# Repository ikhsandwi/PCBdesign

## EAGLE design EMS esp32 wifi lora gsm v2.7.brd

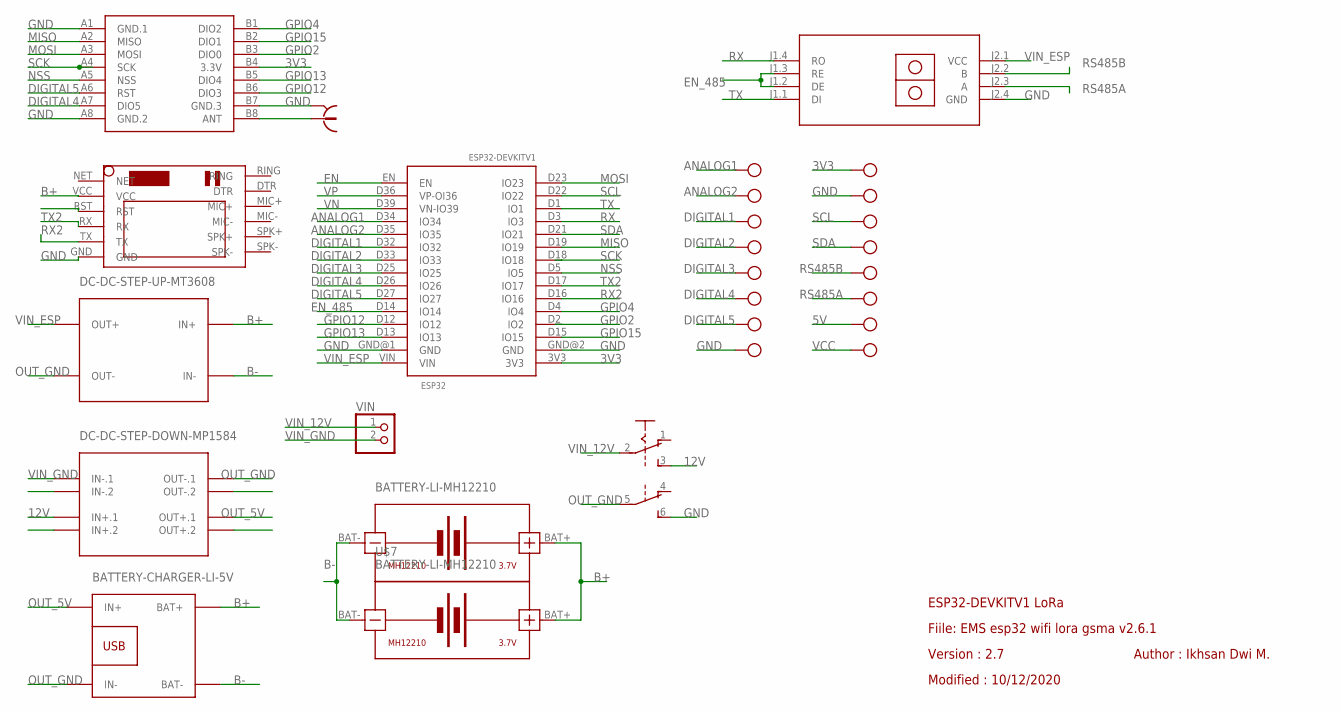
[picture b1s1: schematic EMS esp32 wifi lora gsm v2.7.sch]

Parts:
ESP32: ESP32DEVKITV1; ESP32-DEVKITV1
S1: A68-A31
U$1: RS485-TTL-CONVERTER
U$2: DC-DC-STEP-UP-MT3608
U$3: DC-DC-STEP-DOWN-MP1584
U$4: BATTERY-CHARGER-LI-5V
U$5: WIRELESS-LORA-RFM95W#SMD
U$6, U$7: BATTERY-LI-MH12210
U$9: SIM800LMODULE
VIN: PINHD-1X2; 1X02
X1: 734120110
X2, X3, X4, X5, X6, X7, X8, X9: MKDSN1,5/2-5,08

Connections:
3V3: ESP32.3V3, U$5.B4 (3.3V), X4.1
5V: X9.1
12V: S1.3 (S), U$3.IN+.1
ANALOG1: ESP32.D34 (IO34), X2.1
ANALOG2: ESP32.D35 (IO35), X2.2
B+: U$2.IN+, U$4.BAT+, U$6.BAT+, U$7.BAT+, U$9.VCC
B-: U$2.IN-, U$4.BAT-, U$6.BAT-, U$7.BAT-
DIGITAL1: ESP32.D32 (IO32), X3.1
DIGITAL2: ESP32.D33 (IO33), X3.2
DIGITAL3: ESP32.D25 (IO25), X5.1
DIGITAL4: ESP32.D26 (IO26), U$5.A7 (DIO5), X5.2
DIGITAL5: ESP32.D27 (IO27), U$5.A6 (RST), X6.1
EN: ESP32.EN
EN_485: ESP32.D14 (IO14), U$1.J1.2 (DE), U$1.J1.3 (RE)
GND: ESP32.GND@1 (GND), ESP32.GND@2 (GND), S1.6 (S), U$1.J2.4 (GND), U$5.A1 (GND.1), U$5.A8 (GND.2), U$5.B7 (GND.3), U$9.GND, X1.S@1 (2), X1.S@2 (2), X1.S@3 (2), X4.2, X6.2
GPIO2: ESP32.D2 (IO2), U$5.B3 (DIO0)
GPIO4: ESP32.D4 (IO4), U$5.B1 (DIO2)
GPIO12: ESP32.D12 (IO12), U$5.B6 (DIO3)
GPIO13: ESP32.D13 (IO13), U$5.B5 (DIO4)
GPIO15: ESP32.D15 (IO15), U$5.B2 (DIO1)
MISO: ESP32.D19 (IO19), U$5.A2 (MISO)
MOSI: ESP32.D23 (IO23), U$5.A3 (MOSI)
unnamed: U$5.B8 (ANT), X1.1
NSS: ESP32.D5 (IO5), U$5.A5 (NSS)
OUT_5V: U$3.OUT+.1, U$4.IN+
OUT_GND: S1.5, U$2.OUT-, U$3.OUT-.1, U$4.IN-
RS485A: U$1.J2.3 (A), X8.2
RS485B: U$1.J2.2 (B), X8.1
RX: ESP32.D3 (IO3), U$1.J1.4 (RO)
RX2: ESP32.D16 (IO16), U$9.TX
SCK: ESP32.D18 (IO18), U$5.A4 (SCK)
SCL: ESP32.D22 (IO22), X7.1
SDA: ESP32.D21 (IO21), X7.2
TX: ESP32.D1 (IO1), U$1.J1.1 (DI)
TX2: ESP32.D17 (IO17), U$9.RX
VCC: X9.2
VIN_12V: S1.2, VIN.1
VIN_ESP: ESP32.VIN, U$1.J2.1 (VCC), U$2.OUT+
VIN_GND: U$3.IN-.1, VIN.2
VN: ESP32.D39 (VN-IO39)
VP: ESP32.D36 (VP-OI36)

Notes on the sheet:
ESP32-DEVKITV1 LoRa
Fiile: EMS esp32 wifi lora gsma v2.6.1
Version : 2.7
Modified : 10/12/2020
Author : Ikhsan Dwi M.

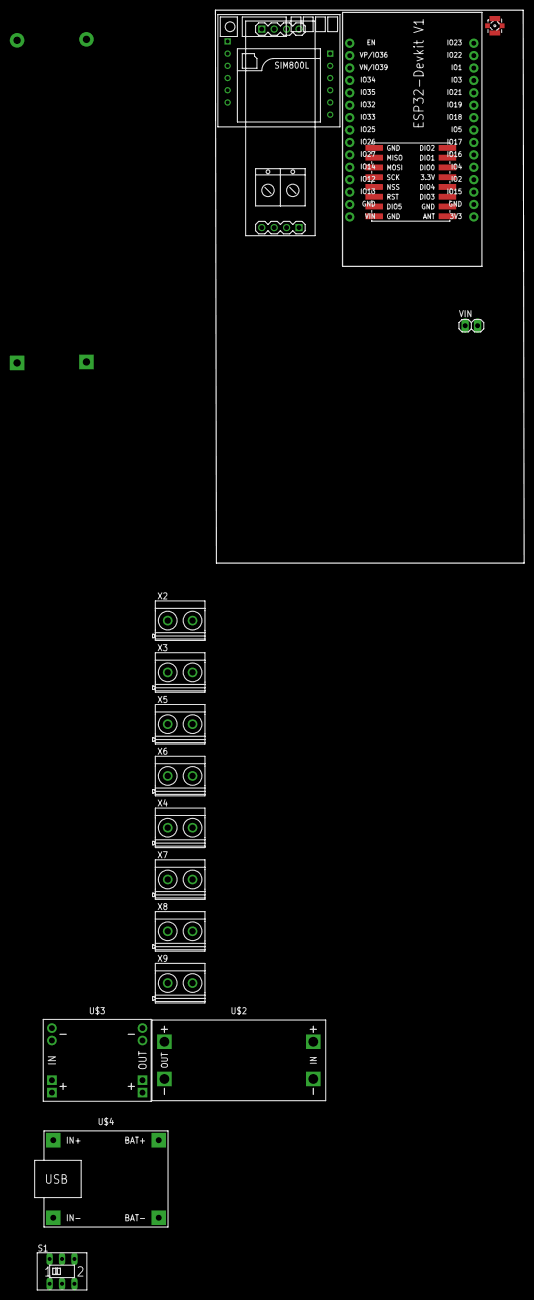
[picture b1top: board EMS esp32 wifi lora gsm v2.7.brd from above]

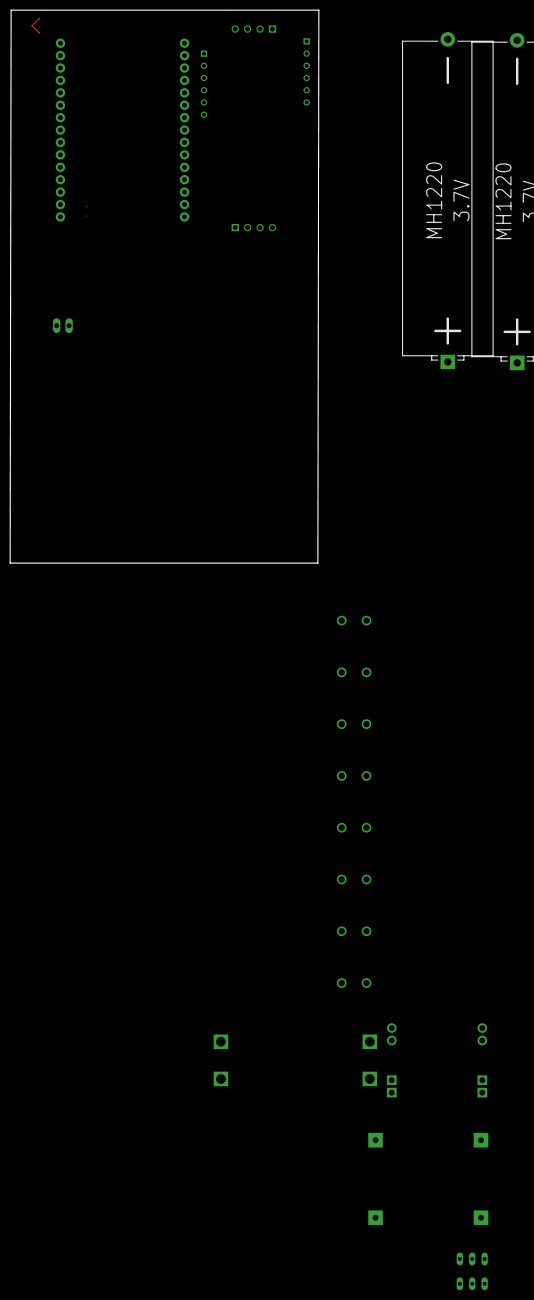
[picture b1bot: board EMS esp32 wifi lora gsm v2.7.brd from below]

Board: 2 copper layers, 63.2 x 113.2 mm, 20 parts (2 on the bottom side), 36 nets.

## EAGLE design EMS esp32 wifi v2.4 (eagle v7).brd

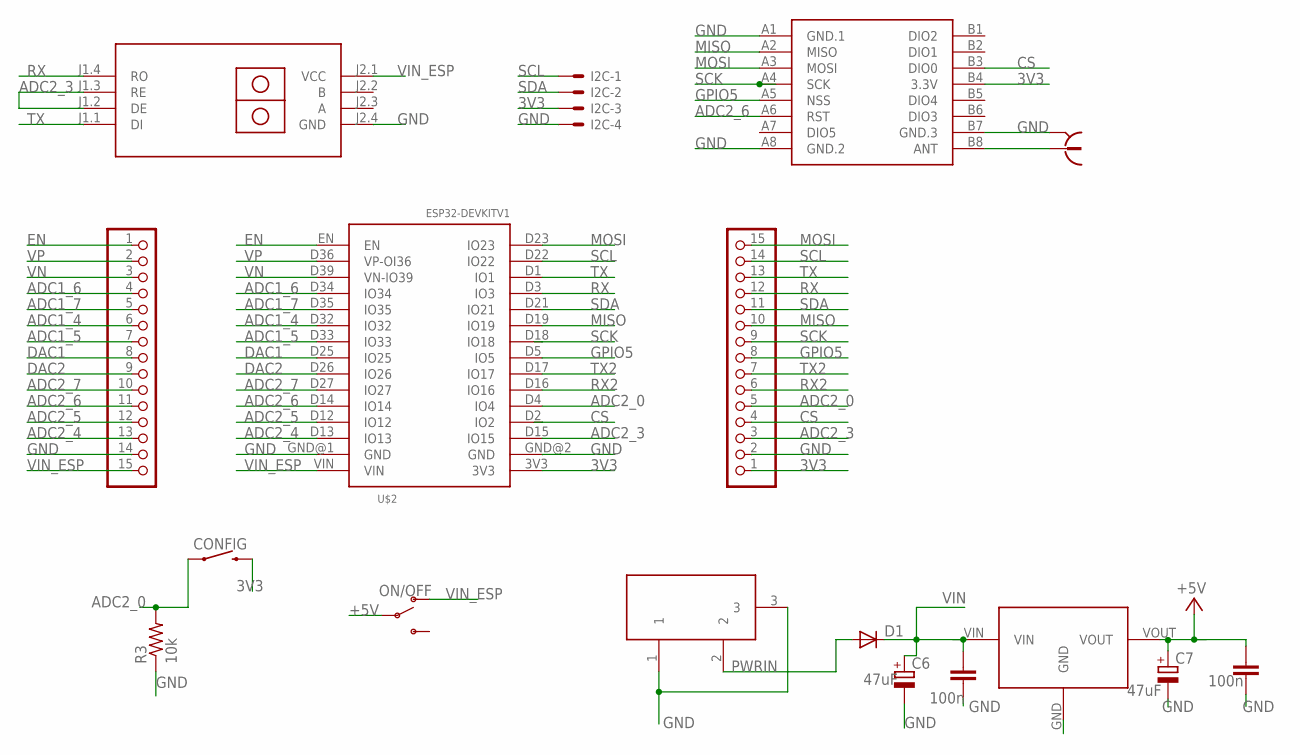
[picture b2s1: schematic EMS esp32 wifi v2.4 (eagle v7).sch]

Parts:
C5, C14: 100n; C1206
C6, C7: 47uF; PANASONIC_D
CONFIG: MOMENTARY-SWITCH-SPST-PTH-6.0MM; TACTILE_SWITCH_PTH_6.0MM
D1: DIODE-SMB; SMB
I2C: 22-23-2041
JP1, JP2: PINHD-1X15; 1X15
ON/OFF: SWITCH-SPDT-PTH-11.6X4.0MM; SWITCH_SPDT_PTH_11.6X4.0MM
R3: 10k; 0204/7
RFM95: WIRELESS-LORA-RFM95W#SMD
U$1: RS485-TTL-CONVERTER
U$2: ESP32DEVKITV1; ESP32-DEVKITV1
U$3: SMARTPRJ_POWERSUPPLY_DC21MMX; SMARTPRJ_POWERSUPPLY_DC-21MM
U$4: 7805-TO263_7805; 7805-TO263_TO263
X1: 734120110

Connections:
3V3: CONFIG.3 (2), I2C.3, JP2.1, RFM95.B4 (3.3V), U$2.3V3
+5V: C7.+, C14.2, ON/OFF.2, U$4.VOUT
ADC1_4: JP1.6, U$2.D32 (IO32)
ADC1_5: JP1.7, U$2.D33 (IO33)
ADC1_6: JP1.4, U$2.D34 (IO34)
ADC1_7: JP1.5, U$2.D35 (IO35)
ADC2_0: CONFIG.1, JP2.5, R3.2, U$2.D4 (IO4)
ADC2_3: JP2.3, U$1.J1.2 (DE), U$1.J1.3 (RE), U$2.D15 (IO15)
ADC2_4: JP1.13, U$2.D13 (IO13)
ADC2_5: JP1.12, U$2.D12 (IO12)
ADC2_6: JP1.11, RFM95.A6 (RST), U$2.D14 (IO14)
ADC2_7: JP1.10, U$2.D27 (IO27)
CS: JP2.4, RFM95.B3 (DIO0), U$2.D2 (IO2)
DAC1: JP1.8, U$2.D25 (IO25)
DAC2: JP1.9, U$2.D26 (IO26)
EN: JP1.1, U$2.EN
GND: C5.1, C6.-, C7.-, C14.1, I2C.4, JP1.14, JP2.2, R3.1, RFM95.A1 (GND.1), RFM95.A8 (GND.2), RFM95.B7 (GND.3), U$1.J2.4 (GND), U$2.GND@1 (GND), U$2.GND@2 (GND), U$3.1, U$3.3, U$4.GND, X1.S@1 (2), X1.S@2 (2), X1.S@3 (2)
GPIO5: JP2.8, RFM95.A5 (NSS), U$2.D5 (IO5)
MISO: JP2.10, RFM95.A2 (MISO), U$2.D19 (IO19)
MOSI: JP2.15, RFM95.A3 (MOSI), U$2.D23 (IO23)
unnamed: RFM95.B8 (ANT), X1.1
PWRIN: D1.A, U$3.2
RX: JP2.12, U$1.J1.4 (RO), U$2.D3 (IO3)
RX2: JP2.6, U$2.D16 (IO16)
SCK: JP2.9, RFM95.A4 (SCK), U$2.D18 (IO18)
SCL: I2C.1, JP2.14, U$2.D22 (IO22)
SDA: I2C.2, JP2.11, U$2.D21 (IO21)
TX: JP2.13, U$1.J1.1 (DI), U$2.D1 (IO1)
TX2: JP2.7, U$2.D17 (IO17)
VIN: C5.2, C6.+, D1.C, U$4.VIN
VIN_ESP: JP1.15, ON/OFF.1 (O), U$1.J2.1 (VCC), U$2.VIN
VN: JP1.3, U$2.D39 (VN-IO39)
VP: JP1.2, U$2.D36 (VP-OI36)

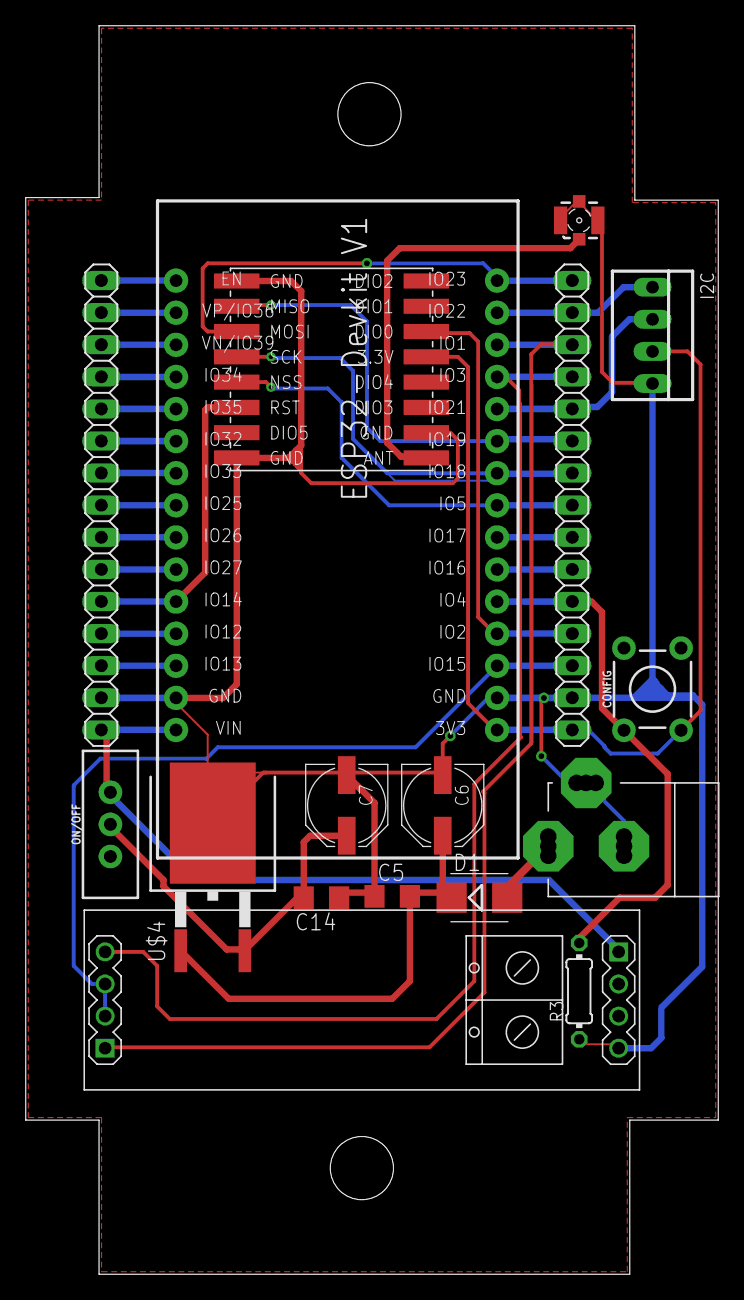
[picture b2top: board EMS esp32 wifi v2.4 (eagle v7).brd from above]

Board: 2 copper layers, 54.8 x 98.8 mm, 17 parts (0 on the bottom side), 33 nets.

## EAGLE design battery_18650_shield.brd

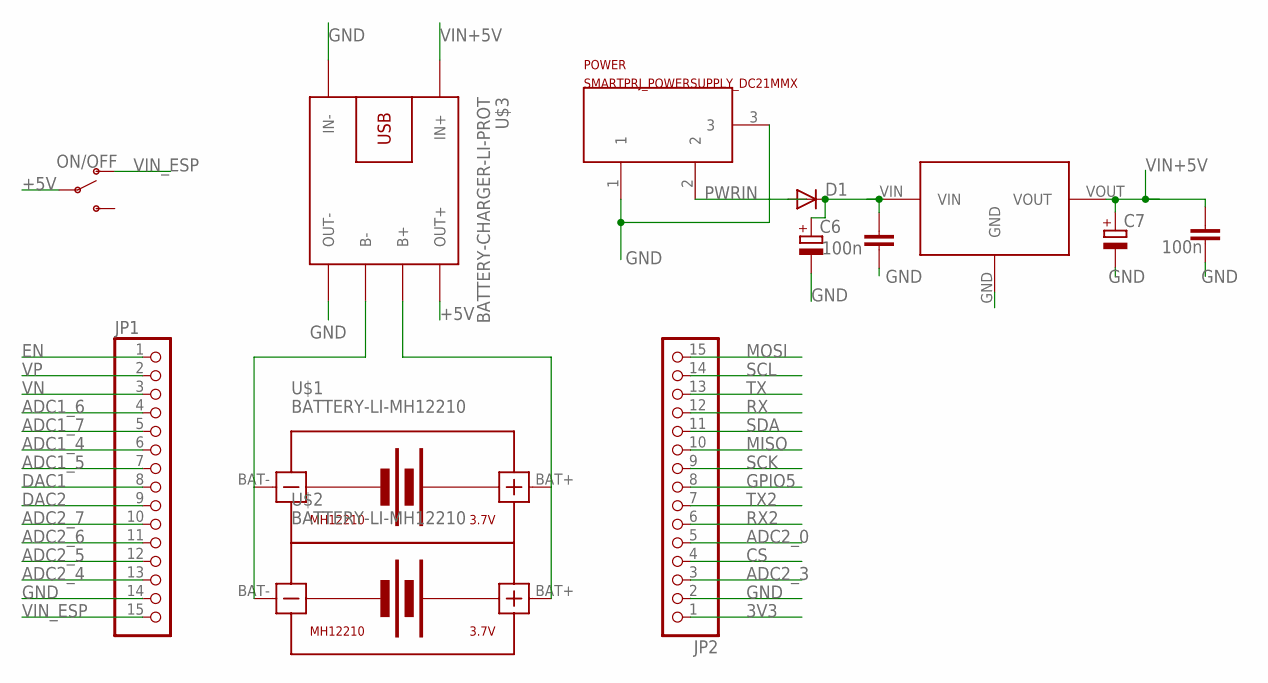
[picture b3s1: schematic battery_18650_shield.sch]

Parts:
C5, C14: 100n; C1206
C6, C7: CPOL-EUD; PANASONIC_D
D1: DIODE-SMB; SMB
JP1, JP2: PINHD-1X15; 1X15
ON/OFF: SWITCH-SPDT-PTH-11.6X4.0MM; SWITCH_SPDT_PTH_11.6X4.0MM
POWER: SMARTPRJ_POWERSUPPLY_DC21MMX; SMARTPRJ_POWERSUPPLY_DC-21MM
U$1, U$2: BATTERY-LI-MH12210
U$3: BATTERY-CHARGER-LI-PROT
U$5: 7805-TO263_7805; 7805-TO263_TO263

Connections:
3V3: JP2.1
+5V: ON/OFF.2, U$3.OUT+
ADC1_4: JP1.6
ADC1_5: JP1.7
ADC1_6: JP1.4
ADC1_7: JP1.5
ADC2_0: JP2.5
ADC2_3: JP2.3
ADC2_4: JP1.13
ADC2_5: JP1.12
ADC2_6: JP1.11
ADC2_7: JP1.10
CS: JP2.4
DAC1: JP1.8
DAC2: JP1.9
EN: JP1.1
GND: C5.1, C6.-, C7.-, C14.1, JP1.14, JP2.2, POWER.1, POWER.3, U$3.IN-, U$3.OUT-, U$5.GND
GPIO5: JP2.8
MISO: JP2.10
MOSI: JP2.15
unnamed: U$1.BAT-, U$2.BAT-, U$3.B-
unnamed: U$1.BAT+, U$2.BAT+, U$3.B+
PWRIN: D1.A, POWER.2
RX: JP2.12
RX2: JP2.6
SCK: JP2.9
SCL: JP2.14
SDA: JP2.11
TX: JP2.13
TX2: JP2.7
VIN: C5.2, C6.+, D1.C, U$5.VIN
VIN+5V: C7.+, C14.2, U$3.IN+, U$5.VOUT
VIN_ESP: JP1.15, ON/OFF.1 (O)
VN: JP1.3
VP: JP1.2

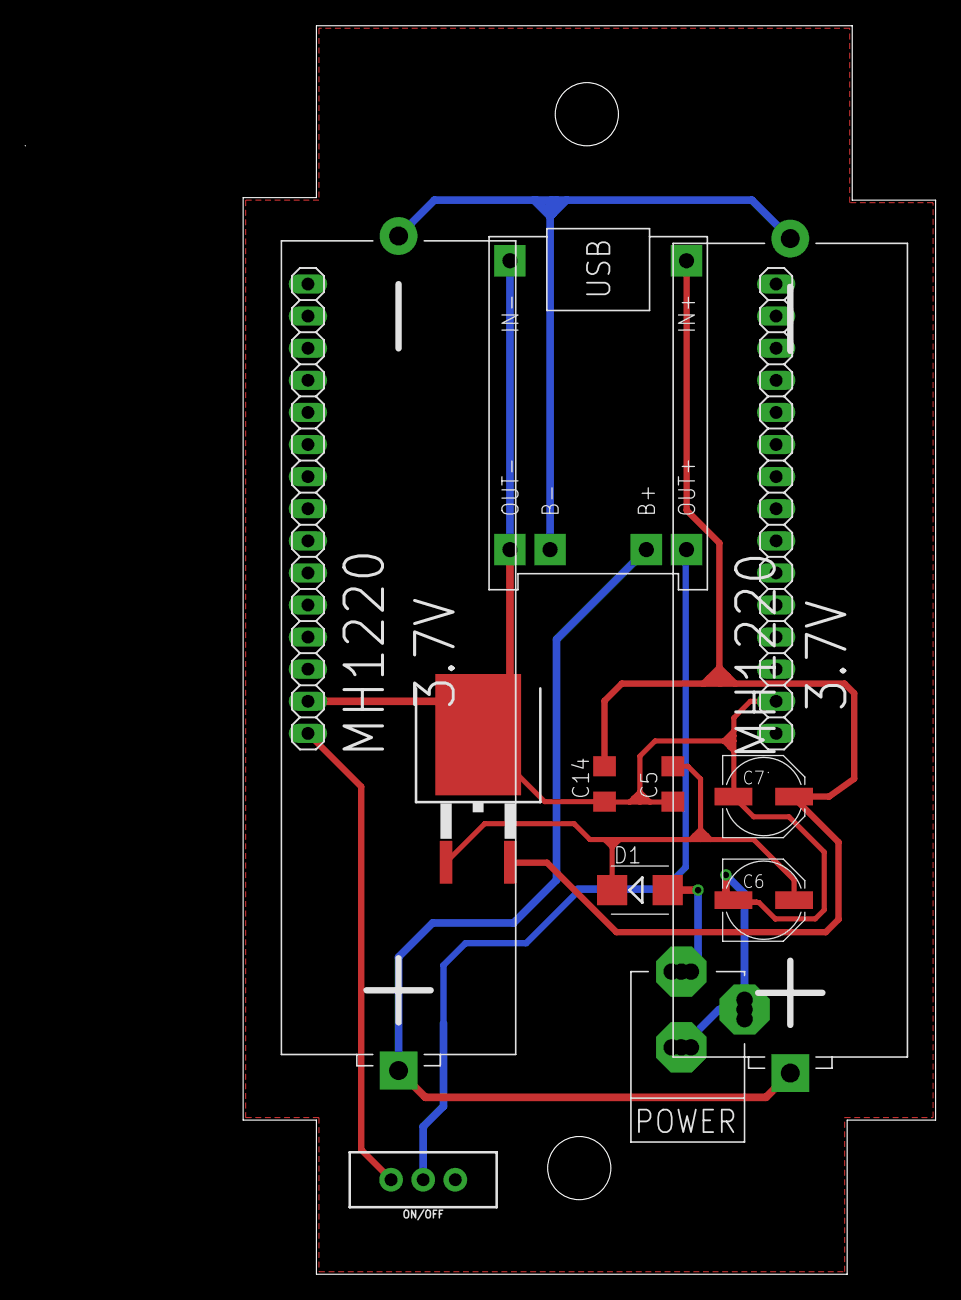
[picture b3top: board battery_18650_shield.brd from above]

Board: 2 copper layers, 54.8 x 98.8 mm, 13 parts (0 on the bottom side), 8 nets.

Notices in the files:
parts and their libraries:
diy-modules: Released under the Creative Commons Attribution 4.0 International License: http://creativecommons.org/licenses/by/4.0
SparkFun-Switches: Licensing: Creative Commons ShareAlike 4.0 International - https://creativecommons.org/licenses/by-sa/4.0
